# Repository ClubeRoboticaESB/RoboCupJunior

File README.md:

# RoboCup Junior

## [Clica aqui para veres a versão Portuguesa](/README_PT.md)
## [Click here to see the English version](/README_EN.md)

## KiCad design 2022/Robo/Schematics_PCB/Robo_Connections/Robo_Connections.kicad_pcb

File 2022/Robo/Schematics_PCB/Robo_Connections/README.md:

# Working on the Schematic/PCB
## ⚠️⚠️Add the STM32 Library and KiCad mod to KiCad⚠️⚠️

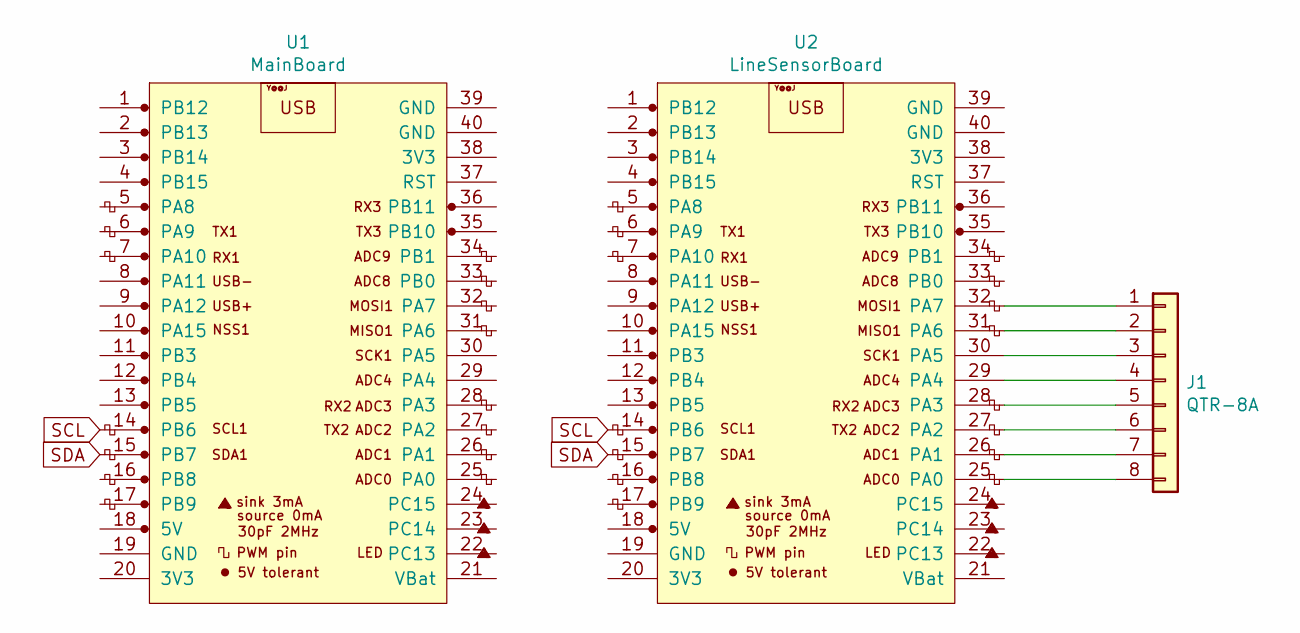
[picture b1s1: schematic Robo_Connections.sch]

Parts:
J1: QTR-8A; JST_EH_S8B-EH_1x08_P2.50mm_Horizontal
U1: MainBoard; YAAJ_BluePill_1
U2: LineSensorBoard; YAAJ_BluePill_1

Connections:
unnamed: J1.1, U2.32 (PA7)
unnamed: J1.2, U2.31 (PA6)
unnamed: J1.3, U2.30 (PA5)
unnamed: J1.4, U2.29 (PA4)
unnamed: J1.5, U2.28 (PA3)
unnamed: J1.6, U2.27 (PA2)
unnamed: J1.7, U2.26 (PA1)
unnamed: J1.8, U2.25 (PA0)
SCL: U1.14 (PB6), U2.14 (PB6)
SDA: U1.15 (PB7), U2.15 (PB7)

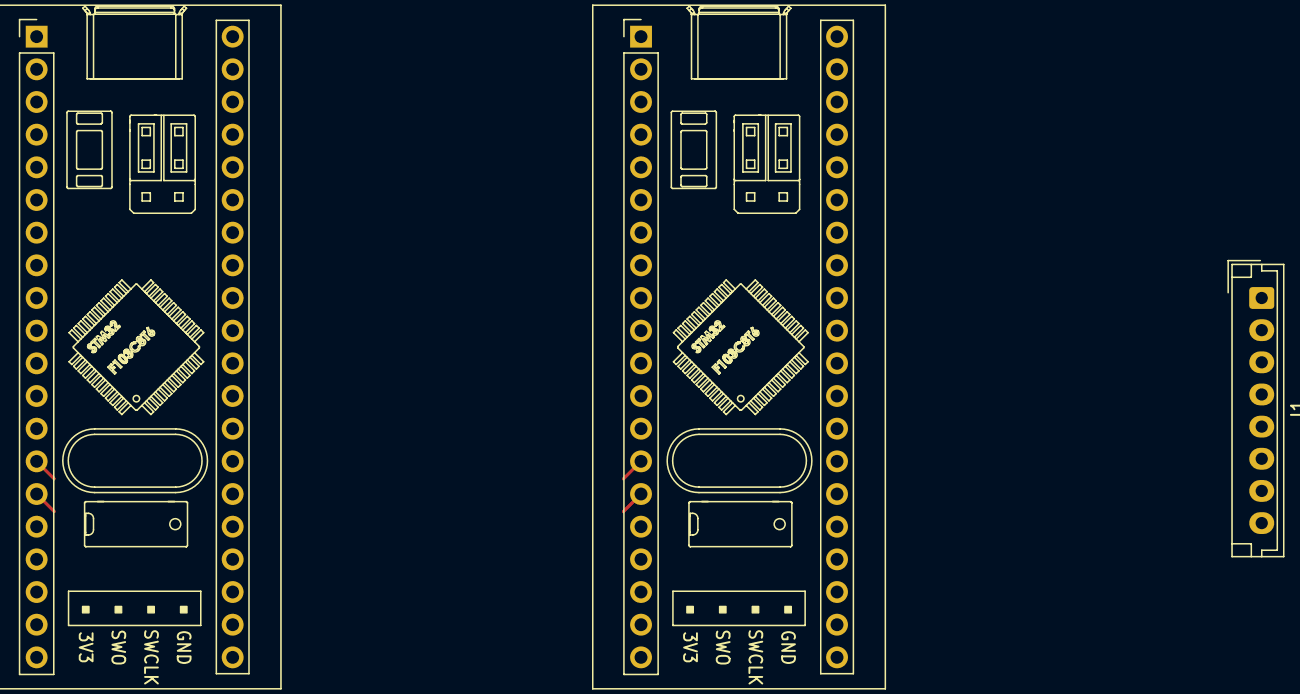
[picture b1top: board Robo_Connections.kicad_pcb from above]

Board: 2 copper layers, 3 parts (0 on the bottom side), 10 nets.

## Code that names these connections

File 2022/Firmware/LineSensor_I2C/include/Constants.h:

//I2C constants
#define SCL_PIN PB8
#define SDA_PIN PB9

// Line Follower QTR-8A constants
// Pins
#define LINE_1_PIN PA0
#define LINE_2_PIN PA1
#define LINE_3_PIN PA2
#define LINE_4_PIN PA3
#define LINE_5_PIN PA4
#define LINE_6_PIN PA5
#define LINE_7_PIN PA6
#define LINE_8_PIN PA7

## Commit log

2021-11-28 Adicionar informações
2021-11-28 Firmware Base
2021-11-28 add new envs and description
2021-12-01 Adicionei noas placas e estrategias
2021-12-02 fix typo
2021-12-02 adicionar novos detalhes
2021-12-02 fix table
2021-12-02 Novo index e retirei a secção sobre o chão
2021-12-02 add new firmware and new info on README
2021-12-02 add new info for the 3.3V reading logic
2021-12-02 new info
2021-12-02 remove tests
2021-12-02 add note about the bootloader on the STM32
2021-12-06 Add new I2C communication
2021-12-08 Chnaged from SPI to I2C and added some test code
2021-12-08 Cleaned up names
2021-12-08 Update README in firmware to reflex changes
2021-12-08 Fix links
2021-12-08 Add Schematics/PCB
2021-12-13 Fix Boards
2021-12-13 Add new example code and update schematics
2021-12-20 add new power circuit
2022-03-14 new additions
2022-03-27 Add libraries for Color sensors and Motor driver
2022-03-27 Update schematic to reflect new pins
2022-03-29 Chnage new pins to allow screen
2022-04-01 change from a Bluepill to a Arduino Mega (due to necessity of more pins)
2022-04-02 update readme's to show new information on comps
2022-04-02 change pins and enviroment to arduino mega
2022-04-05 chnaged enviroment to Arduino Mega and changed the code to do so
2022-04-10 Line Follower Implementation and Turning using sensors started
2022-04-28 Updated Firmware and schematic
2022-04-29 HC-SR04 requires a 20 ms delay
2022-04-29 new code
2022-04-29 Arm and deposit
2022-04-29 new file
2022-04-30 new fix
2022-05-01 changed code
